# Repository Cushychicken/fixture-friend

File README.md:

# fixture-friend

A Kicad 10 design block and board implementation to help make bed-of-nails programming fixtures quickly. Intentionally implemented in this as two layers, so it's cheap and quick to produce assembled at JLCPCB. 

Features:

* 100mm x 100mm board outline
* M3 mounting holes in each corner
* Core RP2040 design as hierarchical sheet 
* Connections to target PCBA and target programming connectors implemented

Design block is fanned out to a few common connector specs, for easy implementation as a reference design:

* SWD: Samtec FTSH 10 pin (standard ARM)
* UART: Molex PicoBlade 4-pin debug connector (keyed differently from QWIIC)
* I2C: QWIIC connector
* SPI: JST-SH 6-pin debug connector

Also included: USB-C to pogo pin interface, to easily land on a set of pogo pins. 

- Note: not tested with USB 2.0 high speed links. Only USB 1.1 operation is assured. 

## RP2040 debug interfaces

The dedicated debug connectors are on the root schematic and are exported from the
`ff-core` hierarchical sheet. They use unassigned RP2040 GPIOs and the following
alternate functions:

| Interface | Connector | Pin order | RP2040 GPIO | RP2040 function |
| --- | --- | --- | --- | --- |
| UART | J8, Molex PicoBlade 53261-0471 | 1 GND, 2 VTREF (+3V3), 3 TX, 4 RX | GPIO4, GPIO5 | UART1 TX (probe to target RX), UART1 RX (target TX to probe) |
| SPI | J9, JST SM06B-SRSS-TB(LF)(SN) | 1 GND, 2 VTREF (+3V3), 3 SCLK, 4 MOSI, 5 MISO, 6 CS_N | GPIO10, GPIO11, GPIO8, GPIO9 | SPI1 SCK, TX, RX, CSn |

J8 uses the KiCad `Connector_Molex` right-angle, 1.25 mm pitch PicoBlade footprint;
its incompatible keying prevents a QWIIC cable from being plugged into UART. J9 uses
the KiCad `Connector_JST` right-angle, 1.00 mm pitch JST-SH footprint. Both are
grouped along accessible board edges. VTREF is a 3.3 V reference output; it is not
intended as an external power input.

The on-board RP2040 is intended to run Raspberry Pi Debug Probe firmware. Its target
SWD engine is GPIO12 (SWCLK drive), GPIO13 (SWD sample input), and GPIO14
(SWD drive); GPIO4/GPIO5 are the firmware's UART1 TX/RX pins. This implementation
is intentionally limited to 3.3 V targets, so GPIO13 and GPIO14 share the target
SWDIO net directly. The RP2040 package
pins named SWCLK and SWDIO are reserved for programming this probe itself and are
not the target-programmer outputs.

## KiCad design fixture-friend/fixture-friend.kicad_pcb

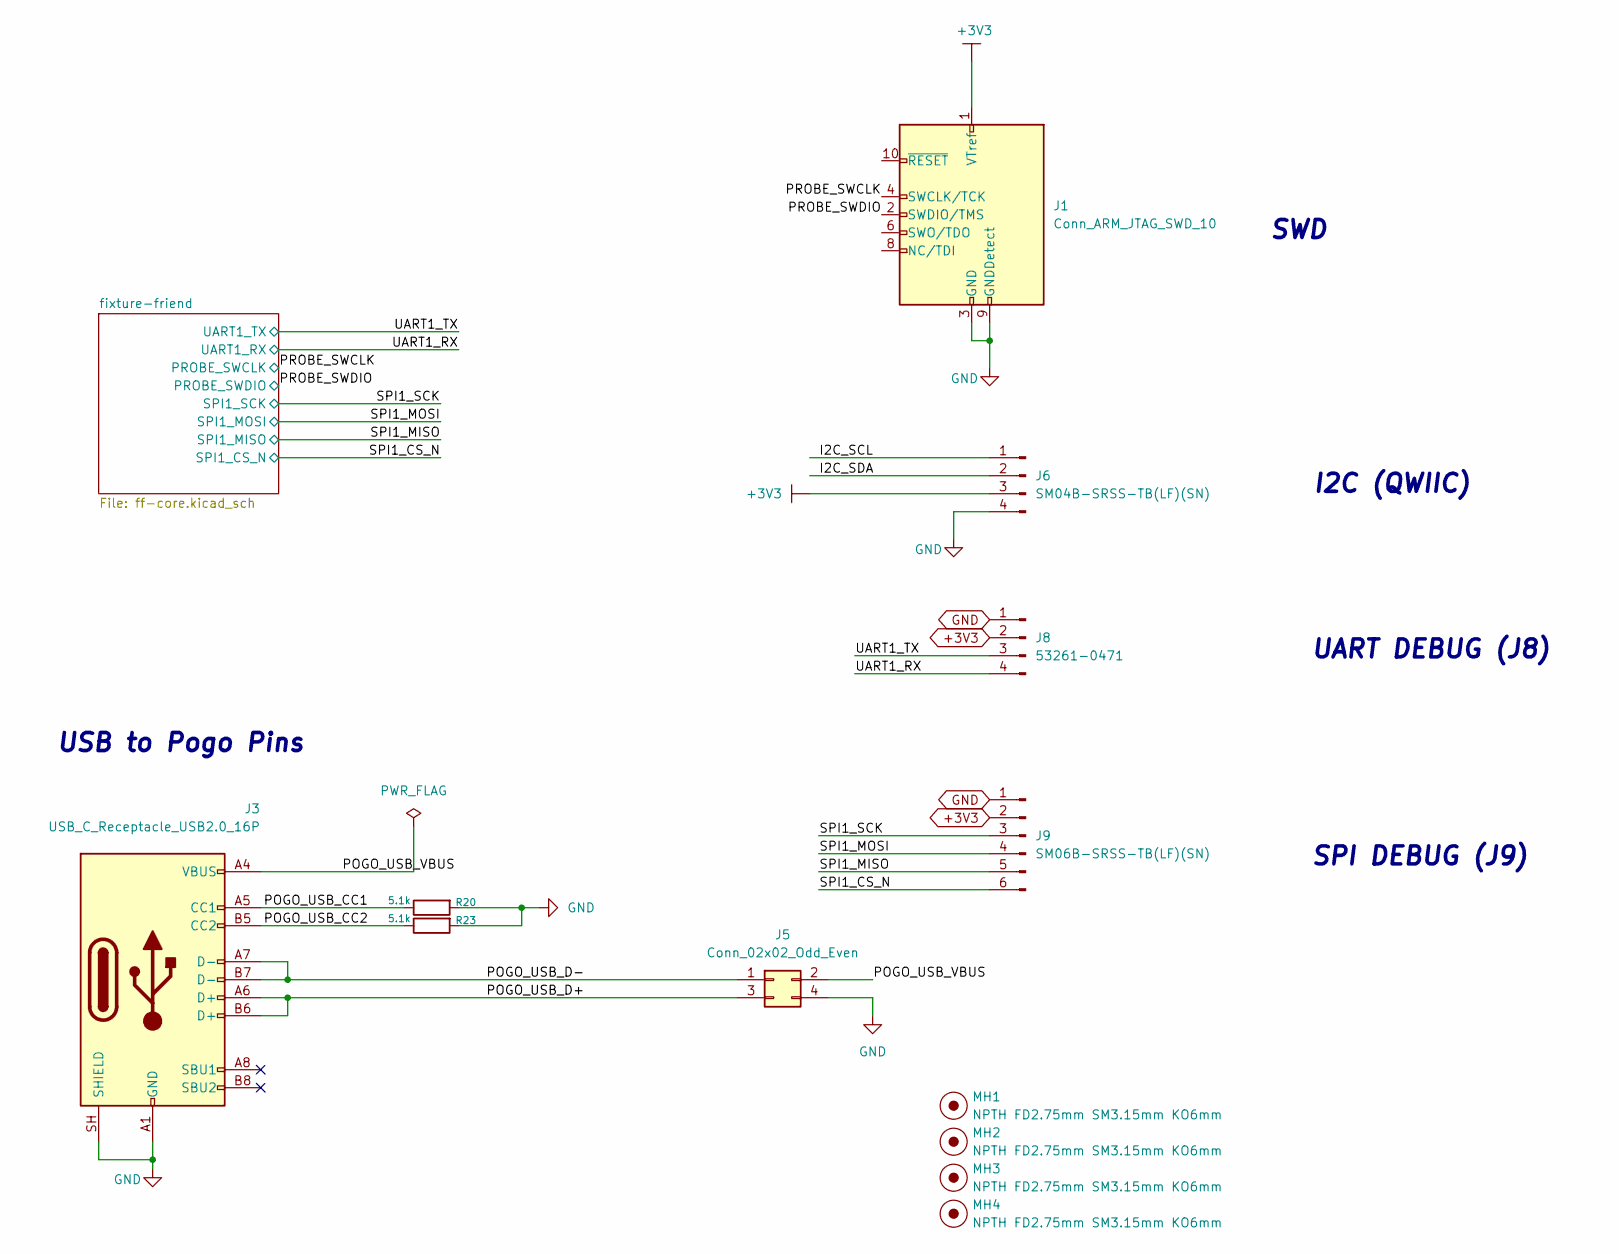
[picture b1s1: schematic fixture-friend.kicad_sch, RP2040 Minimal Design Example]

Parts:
J1: Conn_ARM_JTAG_SWD_10; PinHeader_2x05_P1.27mm_Vertical_SMD
J3: USB_C_Receptacle_USB2.0_16P; USB_C_Receptacle_GCT_USB4085; Manufacturer PN USB4085-GF-A
J5: Conn_02x02_Odd_Even; Harwin_P70-2200045_2x02_P2.54mm; Manufacturer PN P70-2200045
J6: SM04B-SRSS-TB(LF)(SN); JST_SH_SM04B-SRSS-TB_1x04-1MP_P1.00mm_Horizontal
J8: 53261-0471; Molex_PicoBlade_53261-0471_1x04-1MP_P1.25mm_Horizontal; Manufacturer PN 53261-0471
J9: SM06B-SRSS-TB(LF)(SN); JST_SH_SM06B-SRSS-TB_1x06-1MP_P1.00mm_Horizontal; Manufacturer PN SM06B-SRSS-TB(LF)(SN)
MH1, MH2, MH3, MH4: NPTH FD2.75mm SM3.15mm KO6mm; none_mh_npth_fd2p75mm_sm3p15mm_ko6mm; part_uid RP-01HF5R-LCTEJS
R20, R23: 5.1k; R_0603_1608Metric; Manufacturer PN 0603WAF5101T5E

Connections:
+3V3: J1.1 (VTref), J6.3, J8.2, J9.2; also elsewhere on the board
/I2C_SCL: J6.1
/I2C_SDA: J6.2
/POGO_USB_CC1: J3.A5 (CC1), R20.1
/POGO_USB_CC2: J3.B5 (CC2), R23.1
/POGO_USB_D+: J3.A6 (D+), J3.B6 (D+), J5.3
/POGO_USB_D-: J3.A7 (D-), J3.B7 (D-), J5.1
/POGO_USB_VBUS: J3.A4 (VBUS), J3.A9 (VBUS), J3.B4 (VBUS), J3.B9 (VBUS), J5.2
/PROBE_SWCLK: J1.4 (SWCLK/TCK); also elsewhere on the board
/PROBE_SWDIO: J1.2 (SWDIO/TMS); also elsewhere on the board
/SPI1_CS_N: J9.6; also elsewhere on the board
/SPI1_MISO: J9.5; also elsewhere on the board
/SPI1_MOSI: J9.4; also elsewhere on the board
/SPI1_SCK: J9.3; also elsewhere on the board
/UART1_RX: J8.4; also elsewhere on the board
/UART1_TX: J8.3; also elsewhere on the board
GND: J1.3 (GND), J1.5 (GND), J1.9 (GNDDetect), J3.A1 (GND), J3.A12 (GND), J3.B1 (GND), J3.B12 (GND), J3.SH (SHIELD), J5.4, J6.4, J8.1, J9.1, R20.2, R23.2; also elsewhere on the board

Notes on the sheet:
SPI DEBUG (J9)
SWD
USB to Pogo Pins
I2C (QWIIC)
UART DEBUG (J8)

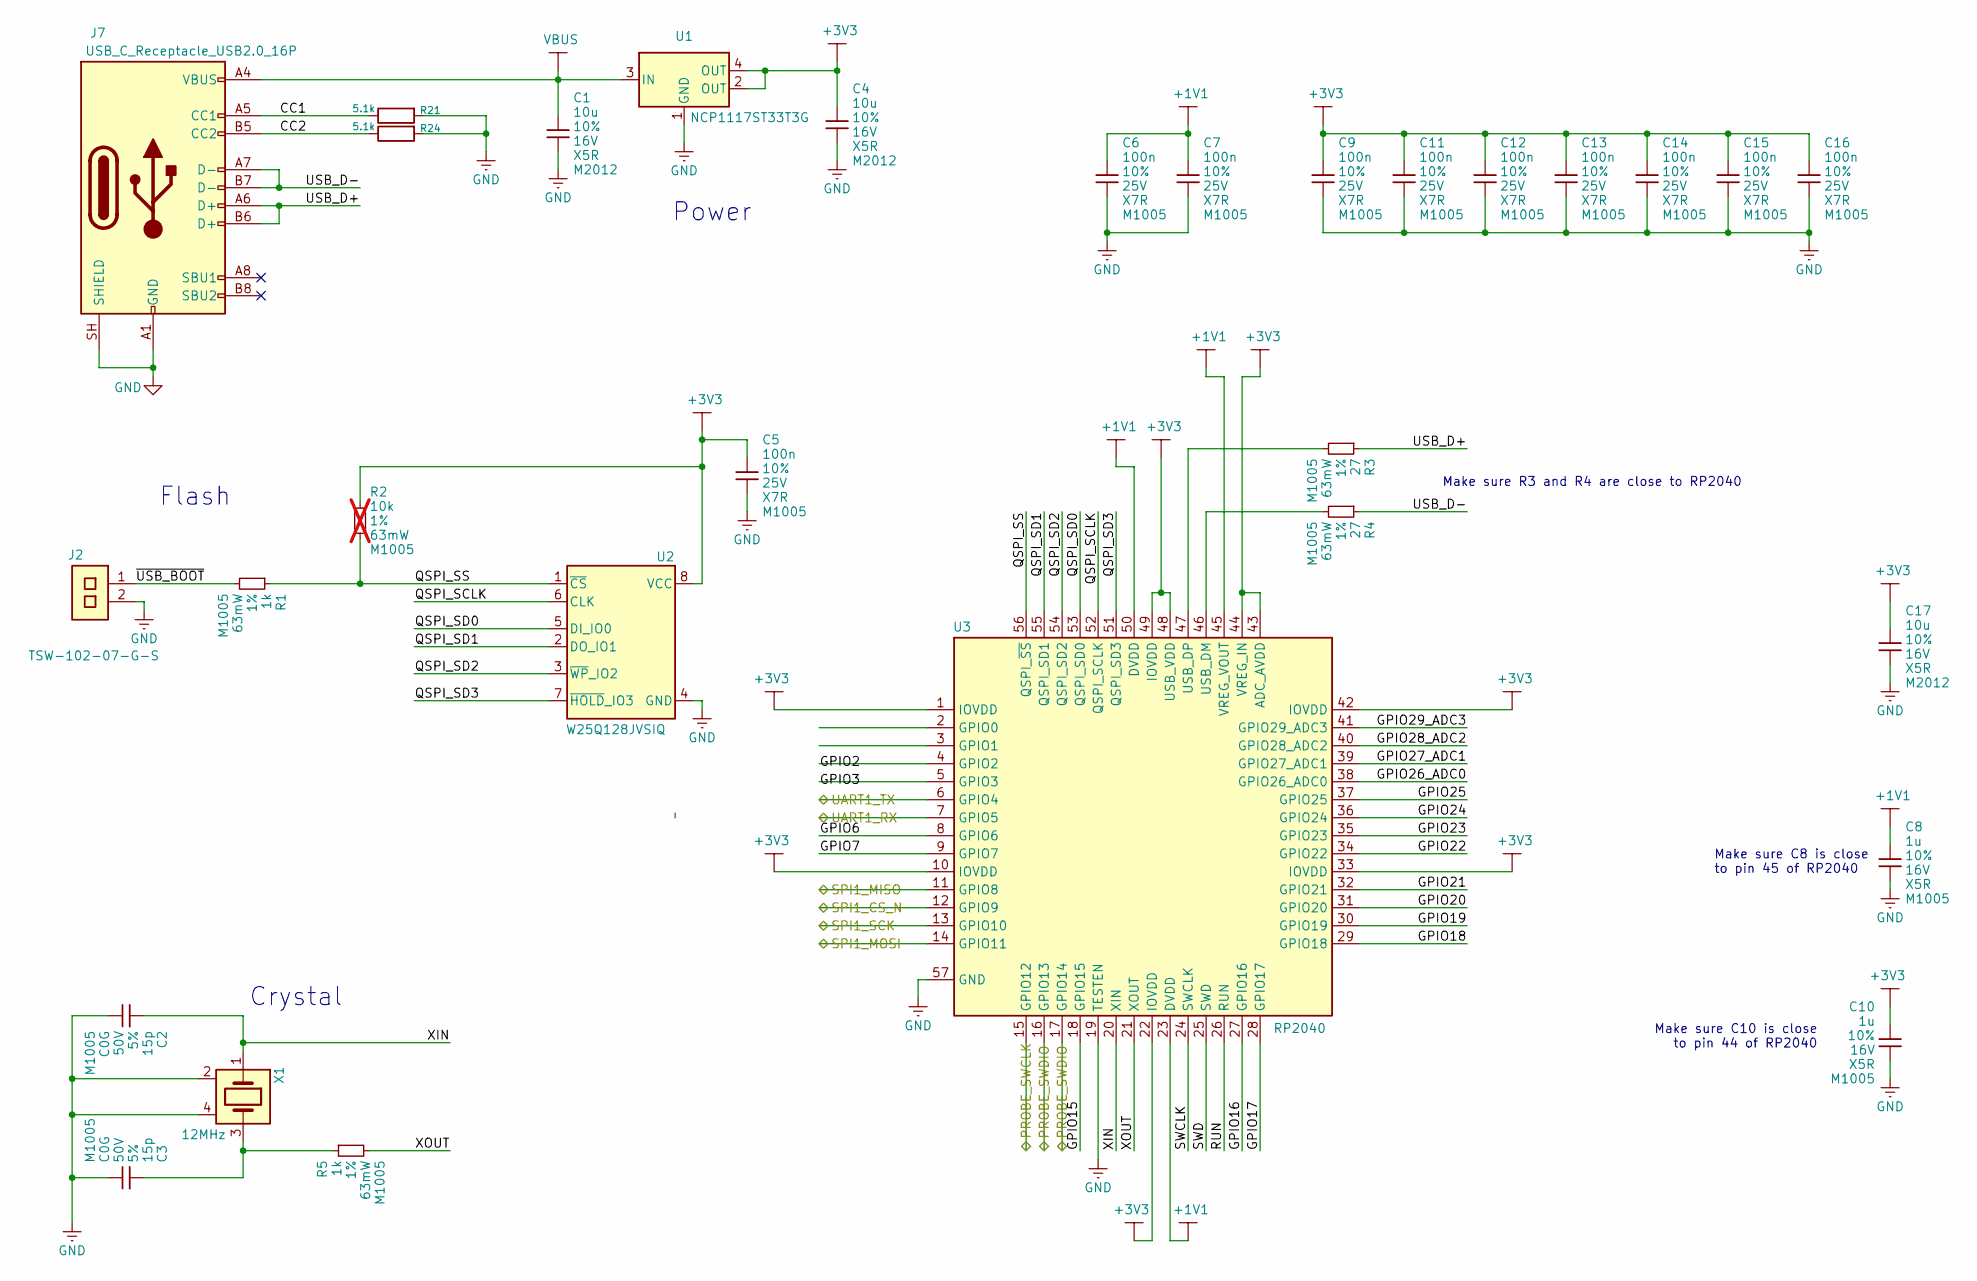
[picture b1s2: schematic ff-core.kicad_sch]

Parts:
C1, C4, C17: 10u; generic_capc2012x125; voltage 16V; tolerance 10%; part_uid RP-01GYSK-AVBE41
C2, C3: 15p; generic_capc1005x50; voltage 50V; tolerance 5%; part_uid RP-01C89W-LLY9XV
C5, C6, C7, C9, C11, C12, C13, C14, C15, C16: 100n; generic_capc1005x50; voltage 25V; tolerance 10%; part_uid RP-01BJ9Y-KRGF41
C8, C10: 1u; generic_capc1005x50; voltage 16V; tolerance 10%; part_uid RP-01GYSK-L7FEKV
J2: TSW-102-07-G-S; samtec_tsw-102-07-g-s; part_uid RP-01JV5X-LY21H5
J7: USB_C_Receptacle_USB2.0_16P; USB_C_Receptacle_GCT_USB4085; Manufacturer PN USB4085-GF-A
R1, R5: 1k; generic_resc1005x35; tolerance 1%; voltage 50V; part_uid RP-019A1P-4Z6ZWY
R2: 10k; generic_resc1005x35; tolerance 1%; voltage 50V; part_uid RP-019A1P-53DHSX; not fitted
R3, R4: 27; generic_resc1005x35; tolerance 1%; voltage 50V; part_uid RP-01C89V-LTEYC4
R21, R24: 5.1k; R_0603_1608Metric; Manufacturer PN 0603WAF5101T5E
U1: NCP1117ST33T3G; onsemi_ncp1117st33t3g; voltage 3.3V; part_uid RP-01JWD9-7JRX6J
U2: W25Q128JVSIQ; generic_soic127p790x195-8; voltage 2.7-3.6V; part_uid RP-01JWD4-F1H4N9
U3: RP2040; rpi_rp2040_vias; part_uid RP-01EKHS-ZTKTEH
X1: 12MHz; generic_xtalcc320x250x80-4; tolerance 30ppm; part_uid RP-01G8X7-GS352B

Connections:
+1V1: C6.1, C7.1, C8.1, U3.23 (DVDD), U3.45 (VREG_VOUT), U3.50 (DVDD)
+3V3: C4.1, C5.1, C9.1, C10.1, C11.1, C12.1, C13.1, C14.1, C15.1, C16.1, C17.1, R2.1, U1.2 (OUT), U1.4 (OUT), U2.8 (VCC), U3.1 (IOVDD), U3.10 (IOVDD), U3.22 (IOVDD), U3.33 (IOVDD), U3.42 (IOVDD), U3.43 (ADC_AVDD), U3.44 (VREG_IN), U3.48 (USB_VDD), U3.49 (IOVDD); also elsewhere on the board
/PROBE_SWCLK: U3.15 (GPIO12); also elsewhere on the board
/PROBE_SWDIO: U3.16 (GPIO13), U3.17 (GPIO14); also elsewhere on the board
/SPI1_CS_N: U3.12 (GPIO9); also elsewhere on the board
/SPI1_MISO: U3.11 (GPIO8); also elsewhere on the board
/SPI1_MOSI: U3.14 (GPIO11); also elsewhere on the board
/SPI1_SCK: U3.13 (GPIO10); also elsewhere on the board
/UART1_RX: U3.7 (GPIO5); also elsewhere on the board
/UART1_TX: U3.6 (GPIO4); also elsewhere on the board
/fixture-friend/CC1: J7.A5 (CC1), R21.1
/fixture-friend/CC2: J7.B5 (CC2), R24.1
/fixture-friend/GPIO2: U3.4 (GPIO2)
/fixture-friend/GPIO3: U3.5 (GPIO3)
/fixture-friend/GPIO6: U3.8 (GPIO6)
/fixture-friend/GPIO7: U3.9 (GPIO7)
/fixture-friend/GPIO15: U3.18 (GPIO15)
/fixture-friend/GPIO16: U3.27 (GPIO16)
/fixture-friend/GPIO17: U3.28 (GPIO17)
/fixture-friend/GPIO18: U3.29 (GPIO18)
/fixture-friend/GPIO19: U3.30 (GPIO19)
/fixture-friend/GPIO20: U3.31 (GPIO20)
/fixture-friend/GPIO21: U3.32 (GPIO21)
/fixture-friend/GPIO22: U3.34 (GPIO22)
/fixture-friend/GPIO23: U3.35 (GPIO23)
/fixture-friend/GPIO24: U3.36 (GPIO24)
/fixture-friend/GPIO25: U3.37 (GPIO25)
/fixture-friend/GPIO26_ADC0: U3.38 (GPIO26_ADC0)
/fixture-friend/GPIO27_ADC1: U3.39 (GPIO27_ADC1)
/fixture-friend/GPIO28_ADC2: U3.40 (GPIO28_ADC2)
/fixture-friend/GPIO29_ADC3: U3.41 (GPIO29_ADC3)
/fixture-friend/QSPI_SCLK: U2.6 (CLK), U3.52 (QSPI_SCLK)
/fixture-friend/QSPI_SD0: U2.5 (DI_IO0), U3.53 (QSPI_SD0)
/fixture-friend/QSPI_SD1: U2.2 (DO_IO1), U3.55 (QSPI_SD1)
/fixture-friend/QSPI_SD2: U2.3 (~WP_IO2), U3.54 (QSPI_SD2)
/fixture-friend/QSPI_SD3: U2.7 (~HOLD_IO3), U3.51 (QSPI_SD3)
/fixture-friend/QSPI_SS: R1.1, R2.2, U2.1 (~CS), U3.56 (QSPI_~SS)
/fixture-friend/RUN: U3.26 (RUN)
/fixture-friend/SWCLK: U3.24 (SWCLK)
/fixture-friend/SWD: U3.25 (SWD)
/fixture-friend/USB_D+: J7.A6 (D+), J7.B6 (D+), R3.1
/fixture-friend/USB_D-: J7.A7 (D-), J7.B7 (D-), R4.1
/fixture-friend/XIN: C2.1, U3.20 (XIN), X1.1
/fixture-friend/XOUT: R5.2, U3.21 (XOUT)
/fixture-friend/~USB_BOOT: J2.1, R1.2
GND: C1.2, C2.2, C3.2, C4.2, C5.2, C6.2, C7.2, C8.2, C9.2, C10.2, C11.2, C12.2, C13.2, C14.2, C15.2, C16.2, C17.2, J2.2, J7.A1 (GND), J7.A12 (GND), J7.B1 (GND), J7.B12 (GND), J7.SH (SHIELD), R21.2, R24.2, U1.1 (GND), U2.4 (GND), U3.19 (TESTEN), U3.57 (GND), X1.2, X1.4; also elsewhere on the board
unnamed: C3.1, R5.1, X1.3
unnamed: R4.2, U3.46 (USB_DM)
unnamed: R3.2, U3.47 (USB_DP)
VBUS: C1.1, J7.A4 (VBUS), J7.A9 (VBUS), J7.B4 (VBUS), J7.B9 (VBUS), U1.3 (IN)

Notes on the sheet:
Flash
Make sure R3 and R4 are close to RP2040
Make sure C10 is close to pin 44 of RP2040
Crystal
Make sure C8 is close to pin 45 of RP2040
Power

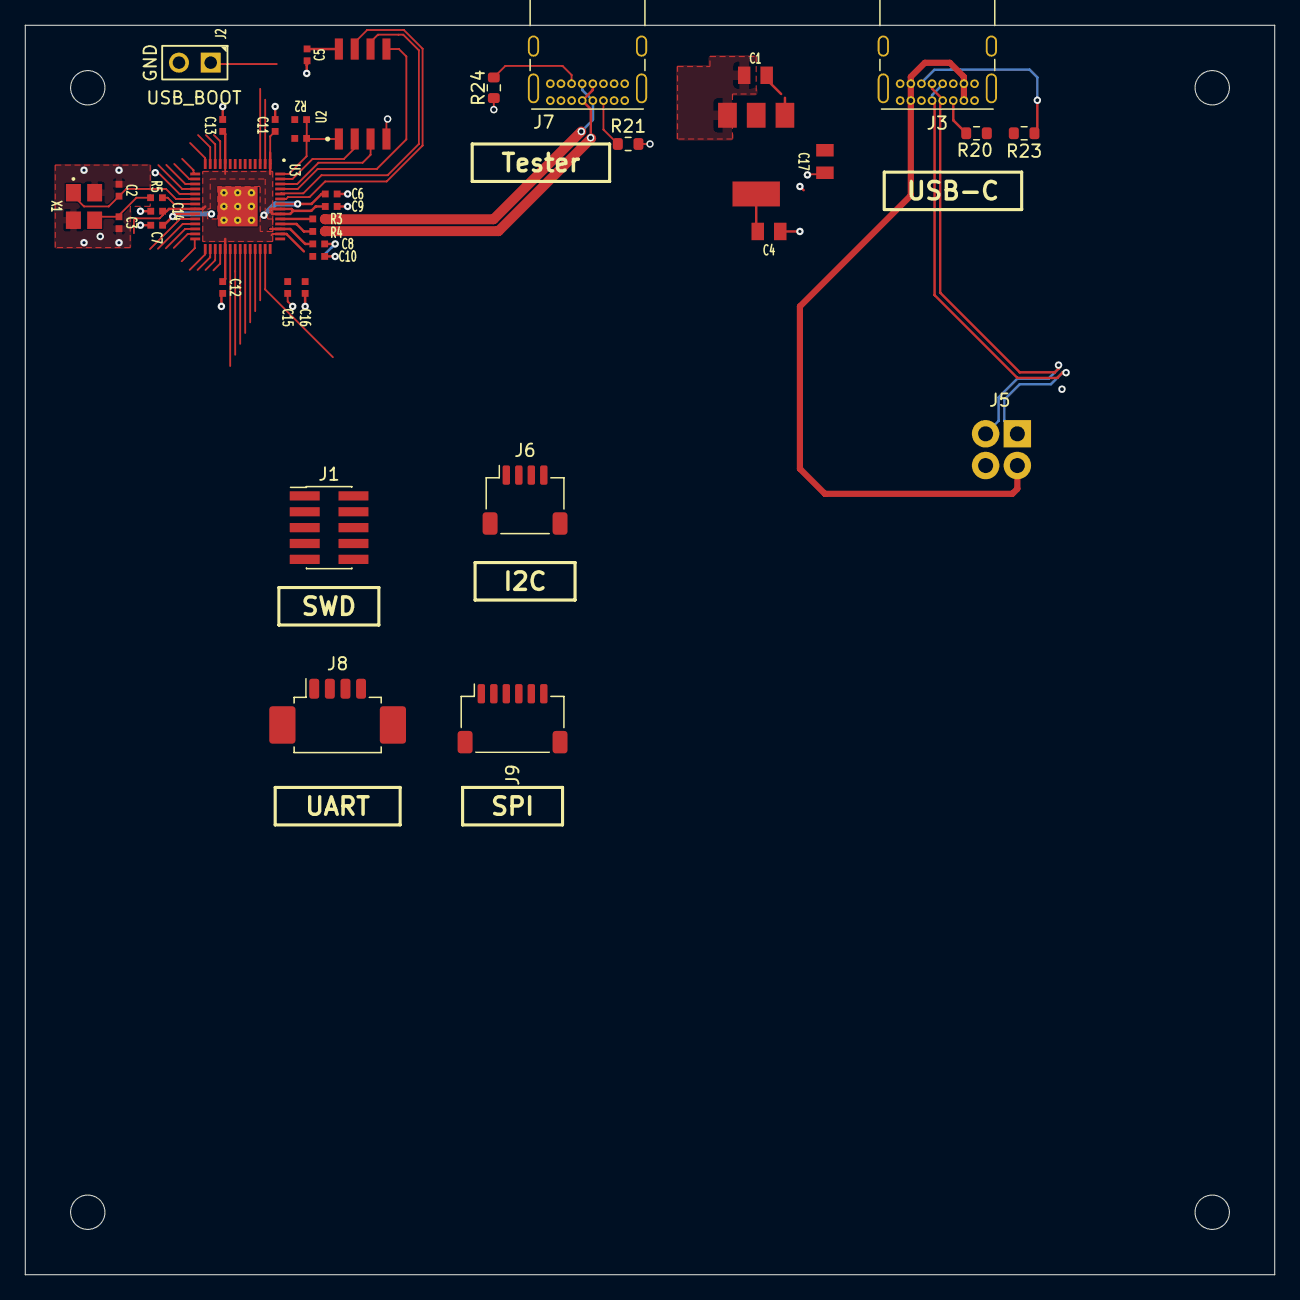
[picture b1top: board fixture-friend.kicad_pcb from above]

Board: 2 copper layers, 100.0 x 100.0 mm, 42 parts (0 on the bottom side), 33 nets.
